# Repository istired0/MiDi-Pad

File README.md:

# MiDi-Pad
MIDI Pad for the 3rd week of Half-Life by Hack-Club
                                                                                                                                                                                  
# Features
- Minimal
- 7-key layout
- RGB LEDs
                                                                                                                                                                                   

# Showcase

# BOM

| Item | Qty | Supplier | Cost/item | Total Cost | Link |
|---|---:|---|---:|---:|---|
| Waveshare ESP32-S3-Zero | 1 | Local | $14.10 | $14.10 | [Link](https://www.local.com) |
| PCB | 1 | JLCPCB | $9.50 | $9.50 | [Link](https://cart.jlcpcb.com/quote/gerberviewThree/?qs=fd7fc4108f3a4beea41fba4c95d3f7fc_1_0_1_0_0.html) |
| EC11 | 2 | AliExpress | $0.69 | $1.38 | [Link](https://www.aliexpress.com/item/1005008773438800.html) |
| Slider | 1 | AliExpress | $2.51 | $2.51 | [Link](https://www.aliexpress.com/item/32556396160.html) |
| LEDs | 1 | AliExpress | $0.77 | $0.77 | [Link](https://www.aliexpress.com/item/1005010491444748.html) |
| Estimated shipping | - | — | — | $0.54 | — |
| **Total** |  |  |  | **$28.80** |  |

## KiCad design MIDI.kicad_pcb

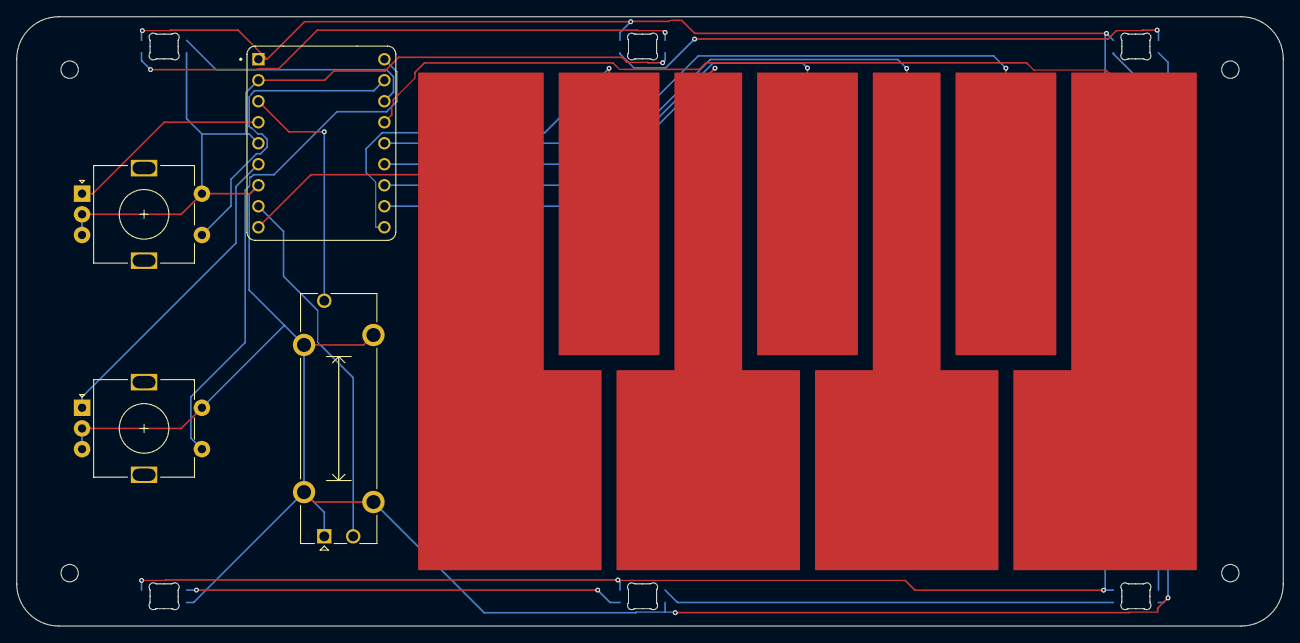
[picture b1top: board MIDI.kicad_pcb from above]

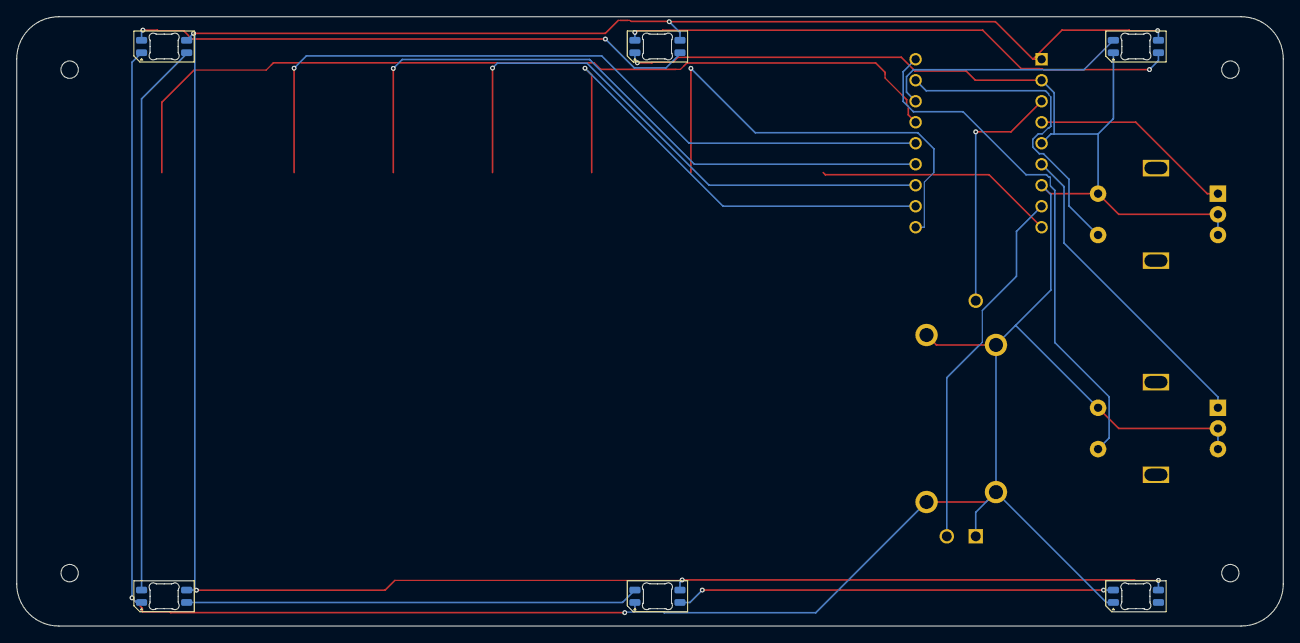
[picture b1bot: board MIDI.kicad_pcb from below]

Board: 2 copper layers, 153.2 x 73.7 mm, 11 parts (6 on the bottom side), 21 nets.

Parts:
D1, D2, D3, D4, D5, D6: SK6812MINI-E; LED_SK6812MINI-E_3.2x2.8mm_P1.5mm_ReverseMount
J1: Conn_01x07_Pin; Pads3
RV1: R_Potentiometer_MountingPin; Potentiometer_Bourns_PTA1543_Single_Slide
SW1, SW2: RotaryEncoder_Switch; RotaryEncoder_Alps_EC11E-Switch_Vertical_H20mm
U1: Waveshare ESP32-S3-ZERO; Waveshare ESP32-S3-Zero

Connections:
+3.3V: RV1.3, U1.3V3 (3V3(OUT))
+5V: D1.3 (VDD), D2.3 (VDD), D3.3 (VDD), D4.3 (VDD), D5.3 (VDD), D6.3 (VDD), U1.5V
/LED: D1.2 (DIN), U1.13 (GP13)
/RE1_A: SW1.A, U1.1 (GP1)
/RE2_A: SW2.A, U1.3 (GP3)
/RSW1: SW1.S1, U1.RX
/RSW2: SW2.S1, U1.TX
/Slider: RV1.2, U1.5 (GP5)
GND: D1.1 (VSS), D2.1 (VSS), D3.1 (VSS), D4.1 (VSS), D5.1 (VSS), D6.1 (VSS), RV1.1, RV1.MP (MountPin), SW1.B, SW1.C, SW1.S2, SW2.B, SW2.C, SW2.S2, U1.2 (GP2), U1.4 (GP4), U1.GND
unnamed: D1.4 (DOUT), D2.2 (DIN)
unnamed: D2.4 (DOUT), D3.2 (DIN)
unnamed: D3.4 (DOUT), D4.2 (DIN)
unnamed: D4.4 (DOUT), D5.2 (DIN)
unnamed: D5.4 (DOUT), D6.2 (DIN)
unnamed: J1.1, U1.6 (GP6)
unnamed: J1.2, U1.7 (GP7)
unnamed: J1.3, U1.8 (GP8)
unnamed: J1.4, U1.9 (GP9)
unnamed: J1.5, U1.10 (GP10)
unnamed: J1.6, U1.11 (GP11)
unnamed: J1.7, U1.12 (GP12)
